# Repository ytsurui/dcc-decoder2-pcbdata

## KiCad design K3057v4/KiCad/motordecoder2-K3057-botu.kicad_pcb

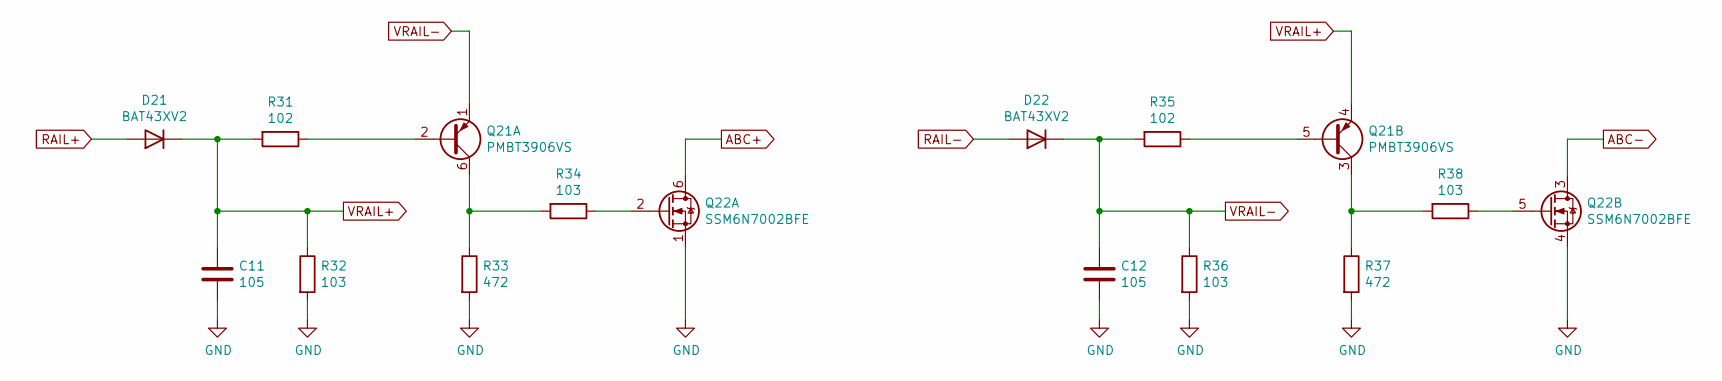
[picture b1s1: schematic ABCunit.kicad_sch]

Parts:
C11, C12: 105; C_1005_v4
D21, D22: BAT43XV2; SOD-523
Q21: PMBT3906VS; SOT-666-nomark-v2
Q22: SSM6N7002BFE; SOT-666-nomark-v2
R31: 102; R_1005_20240411
R32, R36: 103; R_1005_20240411
R33: 472; R_1005_20240411
R34, R38: 103; R_1608_20240411
R35: 102; R_1608_20240411
R37: 472; R_1608_20240411

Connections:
ABC+: Q22.6 (D); also elsewhere on the board
ABC-: Q22.3 (D); also elsewhere on the board
GND: C11.2, C12.2, Q22.1 (S), Q22.4 (S), R32.2, R33.2, R36.2, R37.2; also elsewhere on the board
unnamed: Q21.2 (B1), R31.1
unnamed: Q21.6 (C1), R33.1, R34.2
unnamed: Q21.5 (B2), R35.1
unnamed: Q21.3 (C2), R37.1, R38.2
unnamed: Q22.2 (G), R34.1
unnamed: Q22.5 (G), R38.1
RAIL+: D21.2 (A); also elsewhere on the board
RAIL-: D22.2 (A); also elsewhere on the board
VRAIL+: C11.1, D21.1 (K), Q21.4 (E2), R31.2, R32.1
VRAIL-: C12.1, D22.1 (K), Q21.1 (E1), R35.2, R36.1

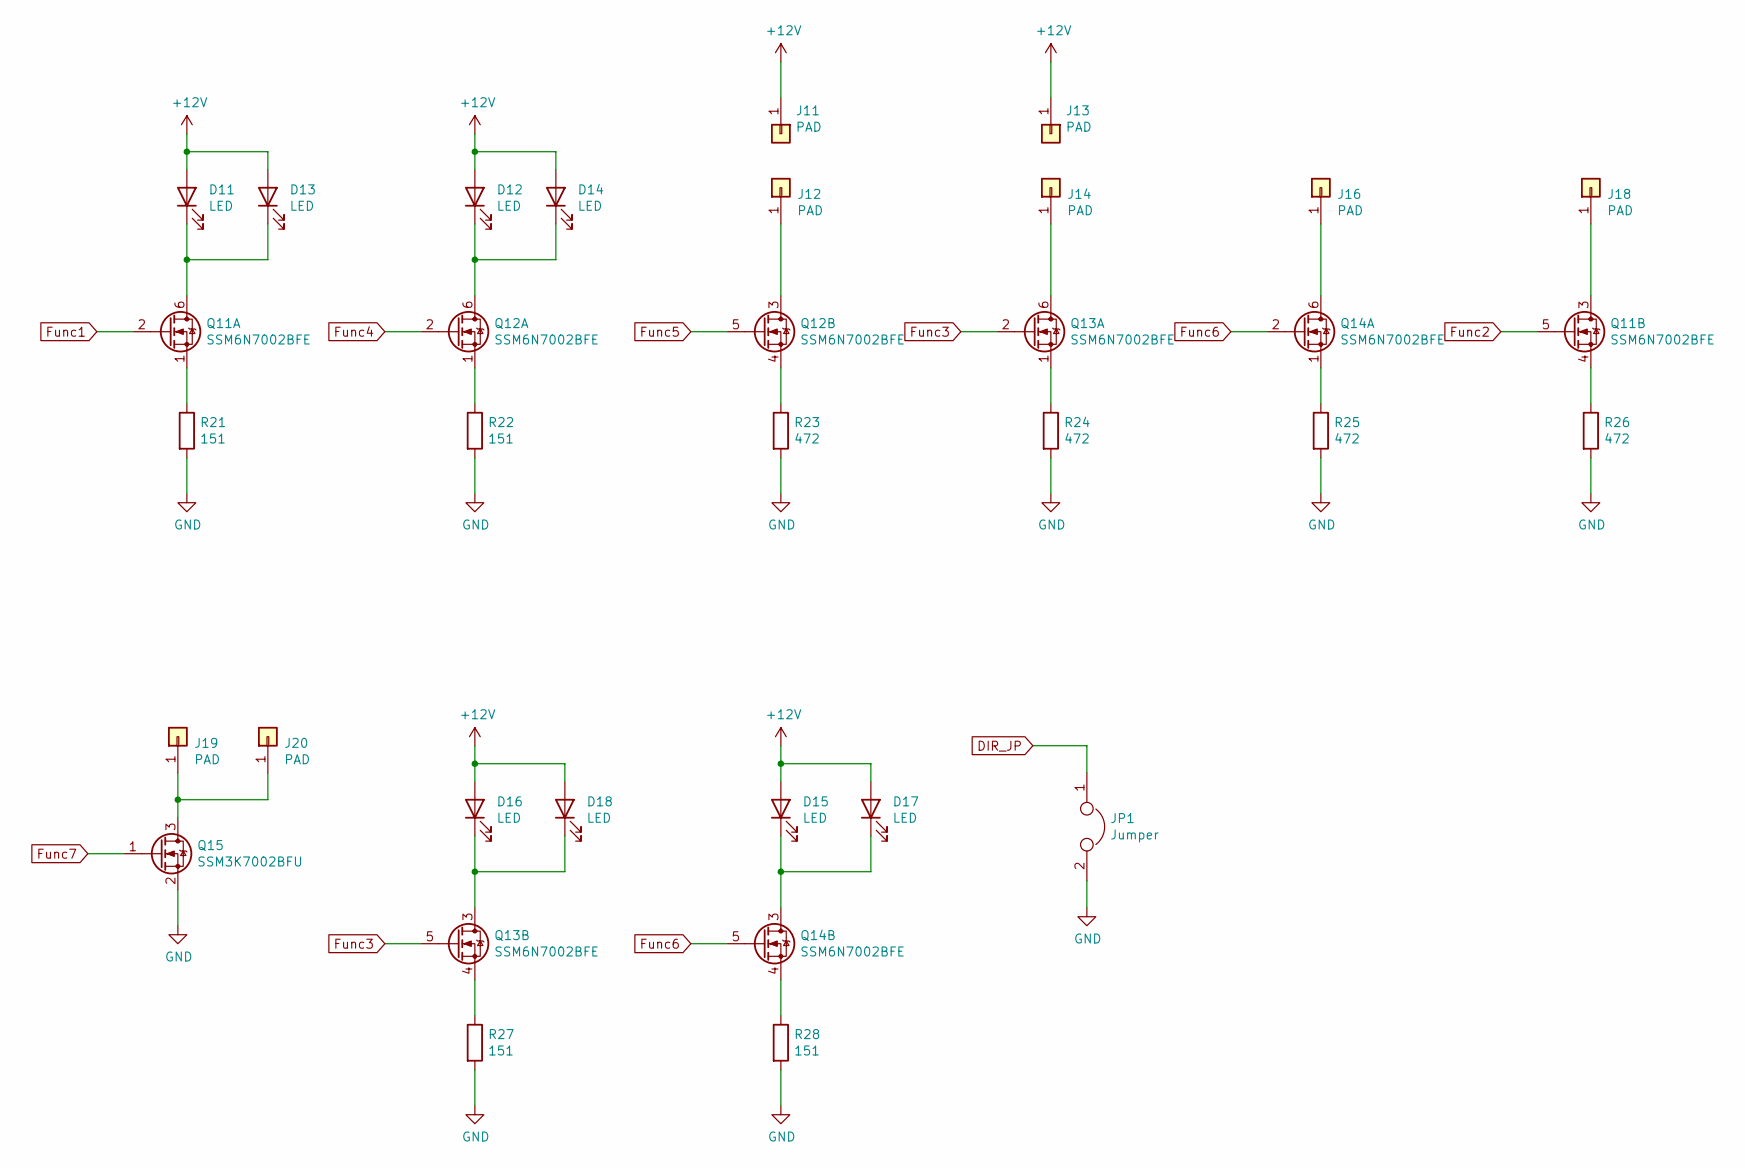
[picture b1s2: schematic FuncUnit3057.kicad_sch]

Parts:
D11, D12, D13, D14, D15, D16, D17, D18: LED; LED_1224_1005_SIDE_BIG2
J11, J13: PAD; PAD_1.0x1.8_SMD
J12, J14, J16, J18: PAD; PAD_1.0x1.0_Hole0.6
J19: PAD; PAD_1.0x1.4_SMD
J20: PAD; PAD_0.5x1.2_SMD
JP1: Jumper; SOLDER_CONN_PAD_0.7mm_1.4mm
Q11, Q12, Q13, Q14: SSM6N7002BFE; SOT-666-nomark-v2
Q15: SSM3K7002BFU; SC-70_v2
R21, R22, R27, R28: 151; R_1608_20240411
R23, R25: 472; R_1005_20240411
R24, R26: 472; R_1608_20240411

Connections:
+12V: D11.2 (A), D12.2 (A), D13.2 (A), D14.2 (A), D15.2 (A), D16.2 (A), D17.2 (A), D18.2 (A), J11.1, J13.1; also elsewhere on the board
DIR_JP: JP1.1; also elsewhere on the board
Func1: Q11.2 (G); also elsewhere on the board
Func2: Q11.5 (G); also elsewhere on the board
Func3: Q13.2 (G), Q13.5 (G); also elsewhere on the board
Func4: Q12.2 (G); also elsewhere on the board
Func5: Q12.5 (G); also elsewhere on the board
Func6: Q14.2 (G), Q14.5 (G); also elsewhere on the board
Func7: Q15.1 (G); also elsewhere on the board
GND: JP1.2, Q15.2 (S), R21.2, R22.2, R23.2, R24.2, R25.2, R26.2, R27.2, R28.2; also elsewhere on the board
unnamed: D11.1 (K), D13.1 (K), Q11.6 (D)
unnamed: D12.1 (K), D14.1 (K), Q12.6 (D)
unnamed: D15.1 (K), D17.1 (K), Q14.3 (D)
unnamed: D16.1 (K), D18.1 (K), Q13.3 (D)
unnamed: J12.1, Q12.3 (D)
unnamed: J14.1, Q13.6 (D)
unnamed: J16.1, Q14.6 (D)
unnamed: J18.1, Q11.3 (D)
unnamed: J19.1, J20.1, Q15.3 (D)
unnamed: Q11.1 (S), R21.1
unnamed: Q11.4 (S), R26.1
unnamed: Q12.1 (S), R22.1
unnamed: Q12.4 (S), R23.1
unnamed: Q13.1 (S), R24.1
unnamed: Q13.4 (S), R27.1
unnamed: Q14.1 (S), R25.1
unnamed: Q14.4 (S), R28.1

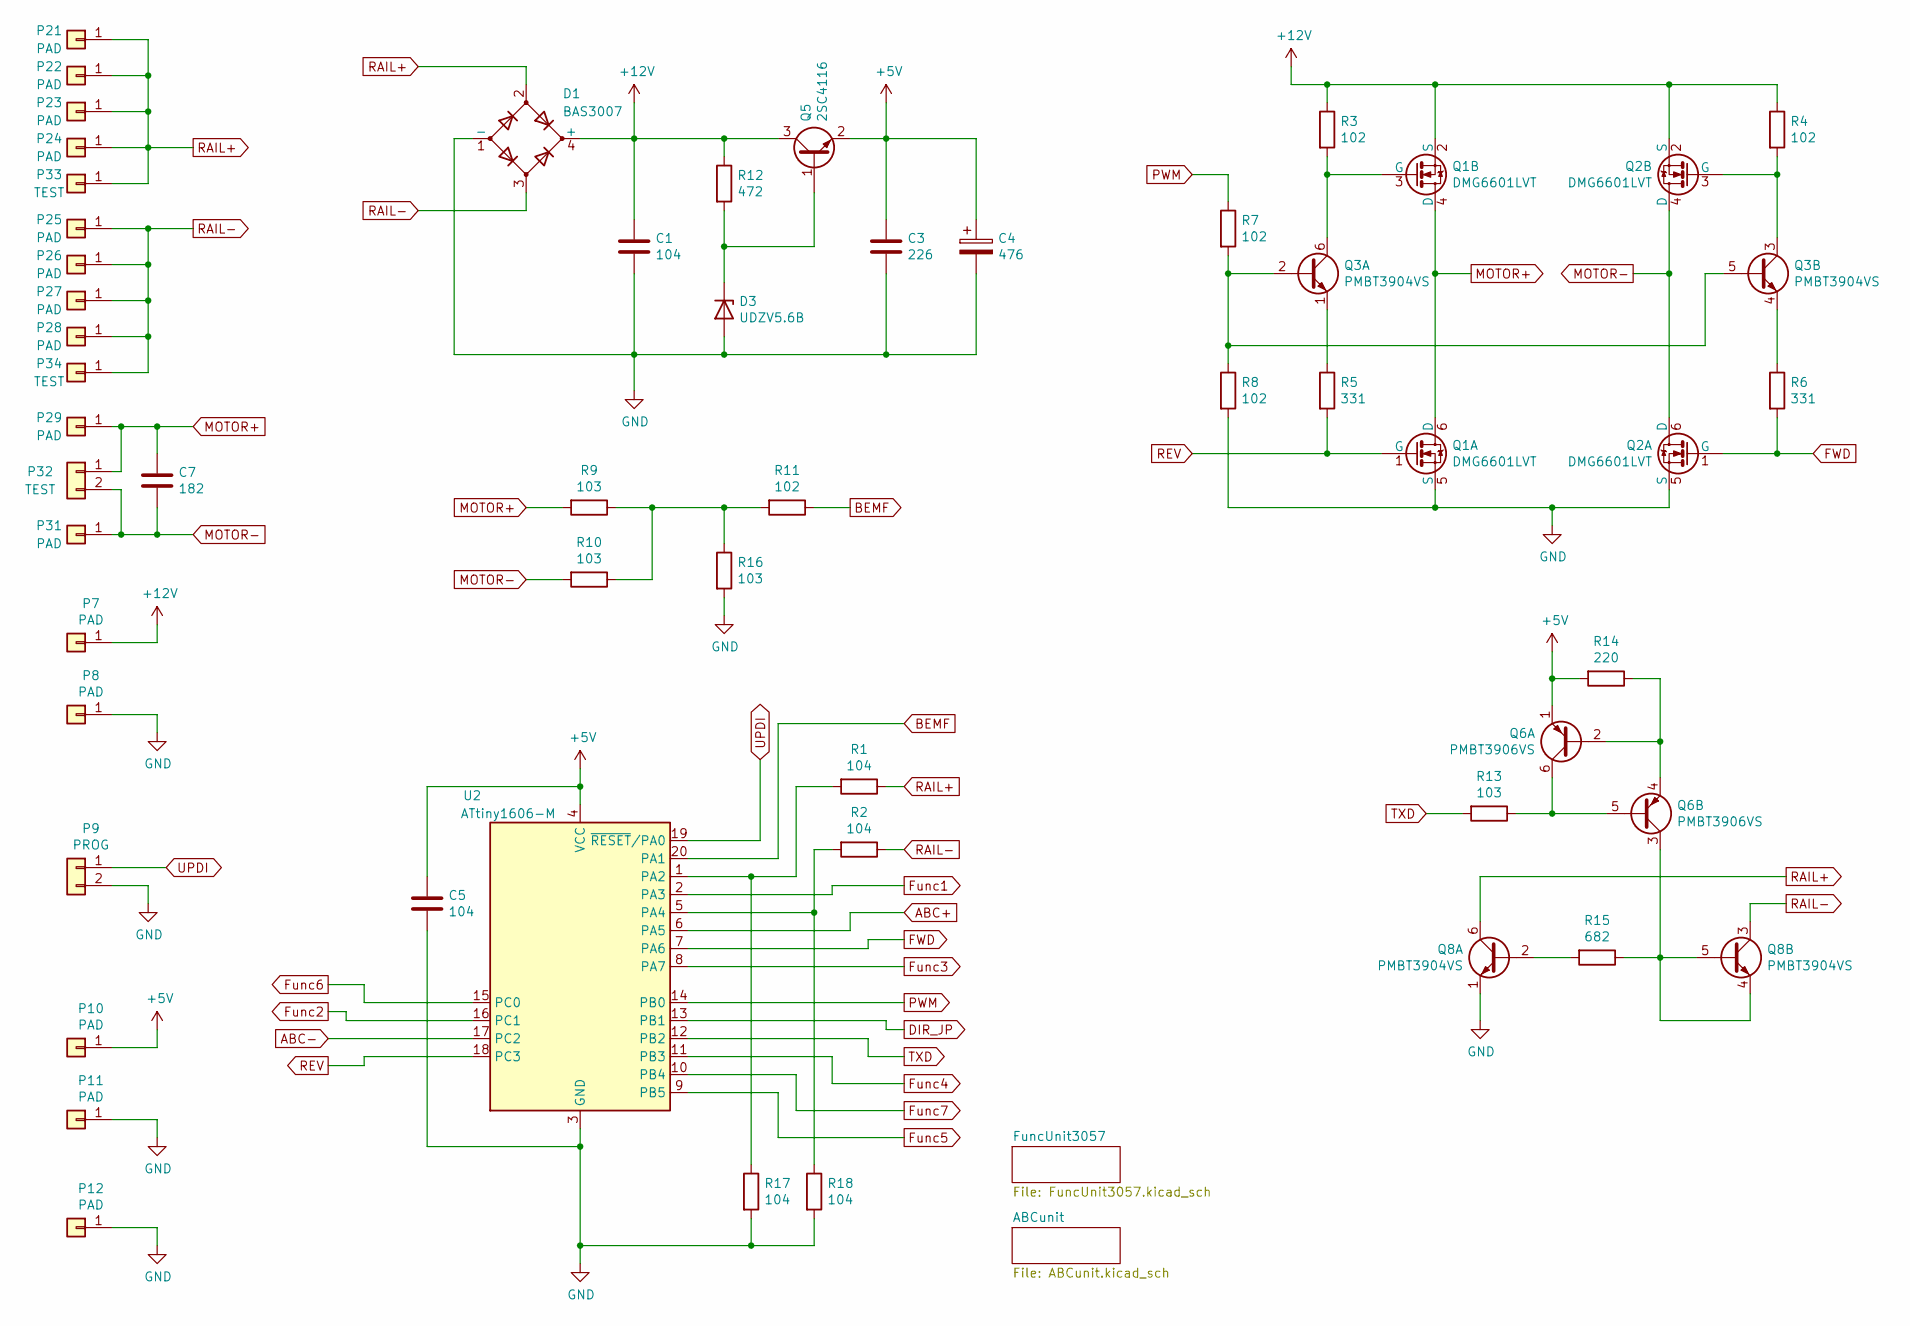
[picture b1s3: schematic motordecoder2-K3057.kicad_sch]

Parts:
C1, C5: 104; C_1005_v4
C3: 226; C_1608_v4
C4: 476; CP_1608
C7: 182; C_1005_v4
D1: BAS3007; SOT-143
D3: UDZV5.6B; UMD2
P7: PAD; PAD_1.0x1.8_SMD
P8, P10: PAD; PAD_0.6x1.0_SMD
P9: PROG; PAD_PROG_2PIN_HOLE0.7
P11: PAD; PAD_0.5x1.2_SMD
P12: PAD; PAD_1.0x1.4_SMD
P21, P24, P25, P28: PAD; KATO_RAILPAD_3057_8mm
P22, P23, P26, P27: PAD; KATO_RAILPAD_3057_7mm
P29, P31: PAD; KATO_MOTORPAD_3057_8mm
P32: TEST; PAD_2mm_2PIN_HOLE0.6
P33, P34: TEST; PAD_1.2x1.2_Hole0.7
Q1, Q2: DMG6601LVT; SOT-23-6-wide
Q3, Q8: PMBT3904VS; SOT-666-nomark-v2
Q5: 2SC4116; SC-70_v2
Q6: PMBT3906VS; SOT-666-nomark-v2
R1, R2, R17, R18: 104; R_1608_20240411
R3, R4, R7, R8: 102; R_1608_20240411
R5, R6: 331; R_1608_20240411
R9, R10, R13: 103; R_1608_20240411
R11: 102; R_1005_20240411
R12: 472; R_1608_20240411
R14: 220; R_1608_20240411
R15: 682; R_1608_20240411
R16: 103; R_1005_20240411
U2: ATtiny1606-M; VQFN-20-1EP_3x3mm_P0.4mm_EP1.7x1.7mm

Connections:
+5V: C3.1, C4.1, C5.1, P10.1, Q5.2 (E), Q6.1 (E1), R14.2, U2.4 (VCC)
+12V: C1.1, D1.4 (+), P7.1, Q1.2 (S), Q2.2 (S), Q5.3 (C), R3.1, R4.1, R12.1; also elsewhere on the board
ABC+: U2.6 (PA5); also elsewhere on the board
ABC-: U2.17 (PC2); also elsewhere on the board
BEMF: R11.1, U2.20 (PA1)
DIR_JP: U2.13 (PB1); also elsewhere on the board
FWD: Q2.1 (G), R6.2, U2.7 (PA6)
Func1: U2.2 (PA3); also elsewhere on the board
Func2: U2.16 (PC1); also elsewhere on the board
Func3: U2.8 (PA7); also elsewhere on the board
Func4: U2.11 (PB3); also elsewhere on the board
Func5: U2.9 (PB5); also elsewhere on the board
Func6: U2.15 (PC0); also elsewhere on the board
Func7: U2.10 (PB4); also elsewhere on the board
GND: C1.2, C3.2, C4.2, C5.2, D1.1 (-), D3.2 (A), P8.1, P9.2, P11.1, P12.1, Q1.5 (S), Q2.5 (S), Q8.1 (E1), R8.2, R16.2, R17.2, R18.2, U2.3 (GND), U2.21 (GND); also elsewhere on the board
MOTOR+: C7.1, P29.1, P32.1, Q1.4 (D), Q1.6 (D), R9.2
MOTOR-: C7.2, P31.1, P32.2, Q2.4 (D), Q2.6 (D), R10.2
unnamed: D3.1 (K), Q5.1 (B), R12.2
unnamed: Q1.3 (G), Q3.6 (C1), R3.2
unnamed: Q2.3 (G), Q3.3 (C2), R4.2
unnamed: Q3.2 (B1), Q3.5 (B2), R7.2, R8.1
unnamed: Q3.1 (E1), R5.1
unnamed: Q3.4 (E2), R6.1
unnamed: Q6.2 (B1), Q6.4 (E2), R14.1
unnamed: Q6.5 (B2), Q6.6 (C1), R13.1
unnamed: Q6.3 (C2), Q8.4 (E2), Q8.5 (B2), R15.1
unnamed: Q8.2 (B1), R15.2
unnamed: R9.1, R10.1, R11.2, R16.1
unnamed: R1.2, R17.1, U2.1 (PA2)
unnamed: R2.2, R18.1, U2.5 (PA4)
PWM: R7.1, U2.14 (PB0)
RAIL+: D1.2, P21.1, P22.1, P23.1, P24.1, P33.1, Q8.6 (C1), R1.1; also elsewhere on the board
RAIL-: D1.3, P25.1, P26.1, P27.1, P28.1, P34.1, Q8.3 (C2), R2.1; also elsewhere on the board
REV: Q1.1 (G), R5.2, U2.18 (PC3)
TXD: R13.2, U2.12 (PB2)
UPDI: P9.1, U2.19 (~RESET/PA0)

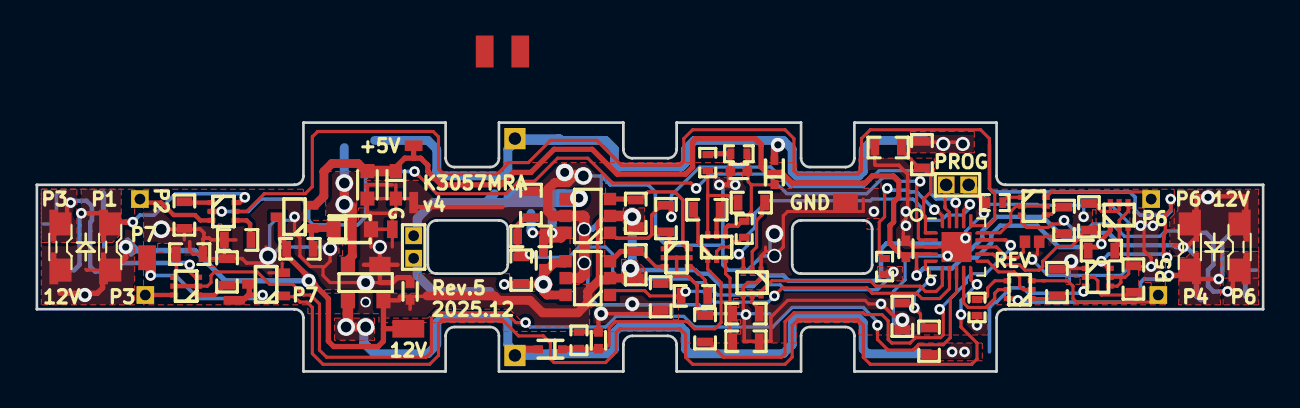
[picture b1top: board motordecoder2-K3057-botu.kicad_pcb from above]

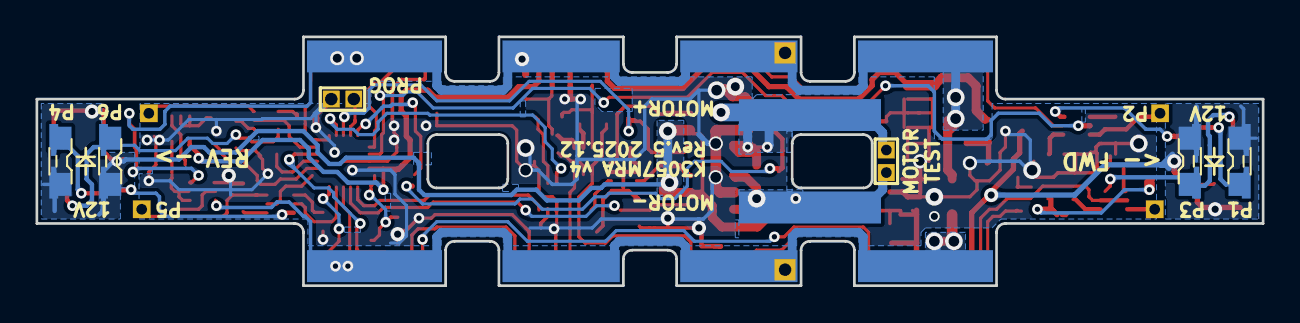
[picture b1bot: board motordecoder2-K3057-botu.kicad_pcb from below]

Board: 2 copper layers, 69.0 x 14.0 mm, 95 parts (4 on the bottom side), 61 nets.
